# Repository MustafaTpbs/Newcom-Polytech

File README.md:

L’observatoire de Nançay a développé un banc de test pour les cartes dites NEWCOM afin de valider leur intégration dans les systèmes finaux. Il y a une soixantaine de cartes qui seront intégrées dans le Radiohéliographe de l’Observatoire Radioastronomique. 
	Le banc de test actuel fonctionne en envoyant des commandes à un générateur de signal qui est relié à un PCB d’interfaçage. L’opérateur branche la carte NEWCOM sur ce PCB d’interfaçage afin d’en observer les sorties sur un logiciel graphique installé sur son PC.
	La problématique : l’opérateur doit systématiquement manipuler un système de câbles volants afin de régler le banc de test sur ce qu’il veut observer. De plus, l’observation se fait sur un logiciel graphique qui affiche les signaux de sortie, donc l’opérateur doit obligatoirement avoir les compétences pour les analyser de lui-même. Cela est également très chronophage, car il doit le faire pour chaque signal, pour chaque carte.

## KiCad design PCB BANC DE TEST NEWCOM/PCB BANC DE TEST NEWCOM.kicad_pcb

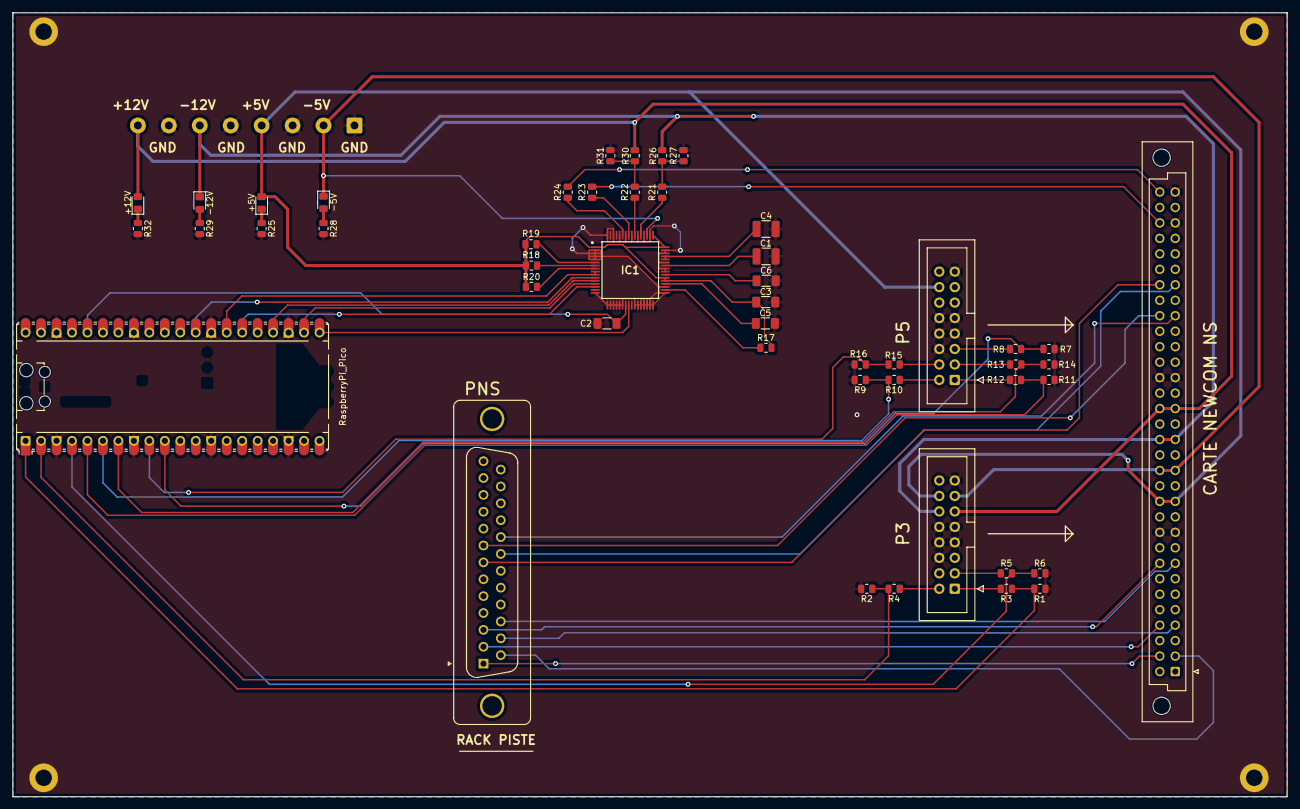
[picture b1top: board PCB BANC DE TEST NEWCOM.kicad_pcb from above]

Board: 2 copper layers, 209.2 x 128.7 mm, 53 parts (1 on the bottom side), 58 nets.

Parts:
+5V, +12V: LED; LED_0805_2012Metric_Pad1.15x1.40mm_HandSolder
-5V, -12V: LED; LED_0805_2012Metric_Pad1.15x1.40mm_HandSolder
A1: RaspberryPi_Pico; RaspberryPi_Pico_Common_Unspecified
C1, C4: 10u; C_1210_3225Metric_Pad1.33x2.70mm_HandSolder
C2, C3: 100n; C_1206_3216Metric_Pad1.33x1.80mm_HandSolder
C5, C6: 1u; C_1206_3216Metric_Pad1.33x1.80mm_HandSolder
CARTE NEWCOM NS: DIN41612_02x32_AB; DIN41612_B_2x32_Female_Vertical_THT
H1, H2, H3, H4: MountingHole_Pad; MountingHole_2.7mm_M2.5_DIN965_Pad
IC1: AD7606BSTZ; QFP50P1200X1200X160-64N
J1, J3: Conn_02x08_Odd_Even; IDC-Header_2x08_P2.54mm_Vertical
J5: Screw_Terminal_01x08; TerminalBlock_Phoenix_MKDS-1,5-8-5.08_1x08_P5.08mm_Horizont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
PNS: DB25_Pins; DSUB-25_Pins_Vertical_P2.77x2.84mm_MountingHoles
R1, R2, R6, R7, R9, R11, R14, R16: 10k; R_0805_2012Metric
R3, R4, R5, R8, R10, R12, R13, R15: 5k; R_0805_2012Metric
R17, R18, R19, R20, R21, R22, R23, R24, R29, R32: 1k; R_0805_2012Metric
R25, R28: 500; R_0805_2012Metric
R26, R30: 3k; R_0805_2012Metric
R27, R31: 9k1; R_0805_2012Metric

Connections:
3V3: A1.36 (3V3), C2.2, IC1.23 (VDRIVE)
100HZ+: CARTE NEWCOM NS.b26, PNS.7
100HZ-: CARTE NEWCOM NS.a26, PNS.20
+5V: +5V.2 (A), C3.2, CARTE NEWCOM NS.a12, CARTE NEWCOM NS.b12, IC1.1 (AVCC_1), IC1.37 (AVCC_2), IC1.38 (AVCC_3), IC1.48 (AVCC_4), IC1.49 (V1), J1.14, J3.14, J5.4, R17.2, R18.2, R19.2, R20.1
+9V(12V): R22.2, R30.2, R31.1
+12V: +12V.2 (A), CARTE NEWCOM NS.a18, CARTE NEWCOM NS.b18, J1.11, J5.8, R30.1
-5V: -5V.1 (K), CARTE NEWCOM NS.a14, CARTE NEWCOM NS.b14, IC1.51 (V2), J1.13, J5.2
-9V(12V): R21.2, R26.2, R27.1
-12V: -12V.1 (K), CARTE NEWCOM NS.a16, CARTE NEWCOM NS.b16, J1.12, J5.6, R26.1
BUSY: A1.26 (GPIO20), IC1.14 (BUSY)
CC1: A1.5 (GPIO3), R11.1, R12.2
CC2: A1.6 (GPIO4), R9.1, R10.2
CC3: A1.7 (GPIO5), R13.2, R14.1
CC4: A1.9 (GPIO6), R15.2, R16.1
CC5: A1.10 (GPIO7), R7.1, R8.2
CK+: CARTE NEWCOM NS.b4, PNS.2
CK-: CARTE NEWCOM NS.a4, PNS.15
CONVST: A1.27 (GPIO21), IC1.9 (CONVST_A), IC1.10 (CONVST_B)
CT1: A1.1 (GPIO0), R1.1, R3.2
CT2: A1.2 (GPIO1), R2.1, R4.2
CT3: A1.4 (GPIO2), R5.2, R6.1
DNS+: CARTE NEWCOM NS.b2, PNS.1
DNS-: CARTE NEWCOM NS.a2, PNS.14
DOUTA: A1.21 (GPIO16), IC1.24 (DB7/DOUTA)
GND: A1.3 (GND), A1.8 (GND), A1.13 (GND), A1.18 (GND), A1.23 (GND), A1.28 (GND), A1.33 (AGND), A1.38 (GND), C1.1, C2.1, C3.1, C4.2, C5.2, C6.2, CARTE NEWCOM NS.a10, CARTE NEWCOM NS.a20, CARTE NEWCOM NS.a30, CARTE NEWCOM NS.a32, CARTE NEWCOM NS.b10, CARTE NEWCOM NS.b20, H1.1, H2.1, H3.1, H4.1, IC1.2 (AGND_1), IC1.3 (OS_0), IC1.4 (OS_1), IC1.5 (OS_2), IC1.16 (DB0), IC1.17 (DB1), IC1.18 (DB2), IC1.19 (DB3), IC1.20 (DB4), IC1.21 (DB5), IC1.22 (DB6), IC1.26 (AGND_2), IC1.27 (DB9), IC1.28 (DB10), IC1.29 (DB11), IC1.30 (DB12), IC1.31 (DB13), IC1.32 (DB14/HBEN), IC1.33 (DB15/BYTE_SEL), IC1.35 (AGND_3), IC1.40 (AGND_4), IC1.41 (AGND_5), IC1.43 (REFGND_1), IC1.46 (REFGND_2), IC1.47 (AGND_6), IC1.50 (V1GND), IC1.52 (V2GND), IC1.54 (V3GND), IC1.56 (V4GND), IC1.58 (V5GND), IC1.60 (V6GND), IC1.62 (V7GND), IC1.64 (V8GND), J1.6, J1.7, J1.8, J1.9, J1.10, J1.15, J3.6, J3.7, J3.8, J3.9, J3.10, J3.15, J5.1, J5.3, J5.5, J5.7, R1.2, R2.2, R6.2, R7.2, R9.2, R11.2, R14.2, R16.2, R25.2, R27.2, R28.2, R29.2, R31.2, R32.2
MODH_NS: CARTE NEWCOM NS.b32, R24.2
MODV_NS: CARTE NEWCOM NS.b30, R23.2
unnamed: +5V.1 (K), R25.1
unnamed: -5V.2 (A), R28.1
unnamed: -12V.2 (A), R29.1
unnamed: +12V.1 (K), R32.1
unnamed: IC1.8 (RANGE), R20.2
unnamed: C4.1, IC1.44 (REFCAPA), IC1.45 (REFCAPB)
unnamed: C1.2, IC1.42 (REFIN/REFOUT)
unnamed: IC1.34 (REF_SELECT), R17.1
unnamed: C5.1, IC1.36 (REGCAP_1)
unnamed: C6.1, IC1.39 (REGCAP_2)
unnamed: IC1.53 (V3), R21.1
unnamed: IC1.55 (V4), R22.1
unnamed: IC1.57 (V5), R23.1
unnamed: IC1.59 (V6), R24.1
unnamed: IC1.6 (~PAR/SER/BYTE_SEL), R19.1
unnamed: IC1.7 (~STBY), R18.1
unnamed: J1.1, R3.1
unnamed: J1.2, R4.1
unnamed: J1.3, R5.1
unnamed: J3.1, R12.1
unnamed: J3.2, R10.1
unnamed: J3.3, R13.1
unnamed: J3.4, R15.1
unnamed: J3.5, R8.1
RESET: A1.29 (GPIO22), IC1.11 (RESET)
SCLK: A1.24 (GPIO18), IC1.12 (~RD/SCLK)
SYNC+: CARTE NEWCOM NS.b24, PNS.8
SYNC-: CARTE NEWCOM NS.a24, PNS.21
VAL+: CARTE NEWCOM NS.b8, PNS.3
VAL-: CARTE NEWCOM NS.a8, PNS.16
~CS: A1.22 (GPIO17), IC1.13 (~CS)

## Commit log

2026-04-02 Deleting history
2026-04-02 correction erreurs de lancement
2026-04-02 Version 1.0, prêt pour la présentation
